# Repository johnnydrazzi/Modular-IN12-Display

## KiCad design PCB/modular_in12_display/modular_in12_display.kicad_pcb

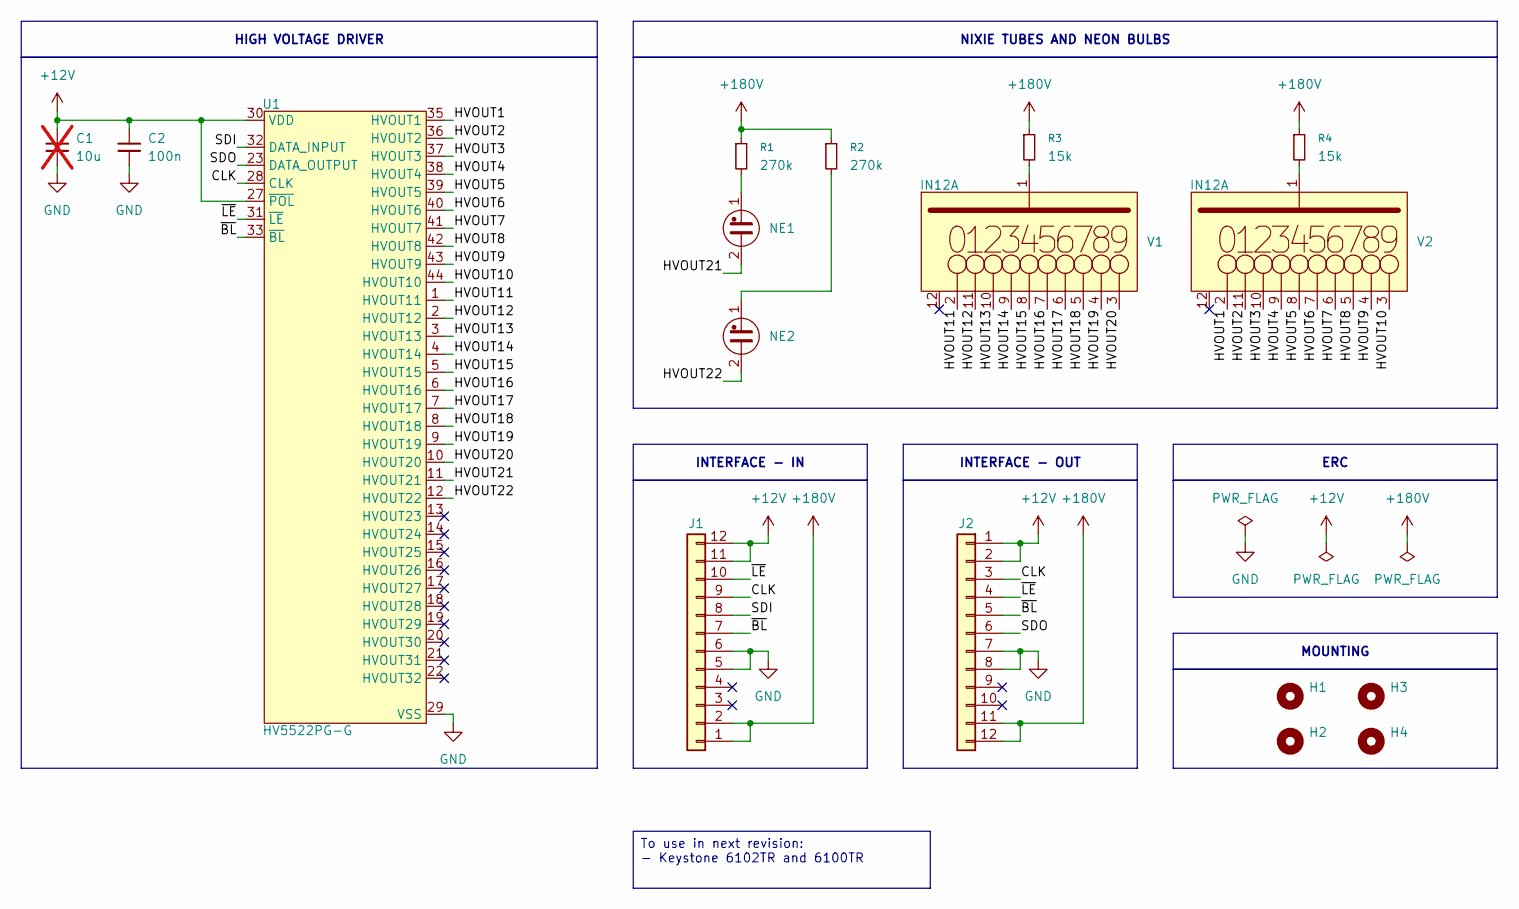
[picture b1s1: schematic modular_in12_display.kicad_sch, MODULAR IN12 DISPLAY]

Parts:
C1: 10u; C_1206_3216Metric; MPN CL31B106KBHNNNE; LCSC C89632; not fitted
C2: 100n; C_0805_2012Metric; MPN CL21B104KBCNNNC; LCSC C1711
H1, H2, H3, H4: MountingHole; MountingHole_3.2mm_M3_Pad
J1: IDC 10P Male Edge; MPN ZX-PZ2.54-2-6PZZ; LCSC C7501277
J2: IDC 10P Female Edge; MPN PM254-2-06-Z-8.5; LCSC C2897407
NE1, NE2: Lamp_Neon; Generic Neon Bulb; MPN INS-1
R1, R2: 270k; R_0805_2012Metric; MPN 0805W8F2703T5E; LCSC C17589
R3, R4: 15k; R_1206_3216Metric; MPN 1206W4F1502T5E; LCSC C25828
U1: HV5522PG-G; PQFP-44_10x10mm_P0.8mm; MPN HV5522PG-G
V1, V2: IN12A

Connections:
+12V: C1.1, C2.1, J1.11, J1.12, J2.1, J2.2, U1.27 (~POL), U1.30 (VDD)
+180V: J1.1, J1.2, J2.11, J2.12, R1.1, R2.1, R3.1, R4.1
/CLK: J1.9, J2.3, U1.28 (CLK)
/HVOUT1: U1.35 (HVOUT1), V2.2
/HVOUT2: U1.36 (HVOUT2), V2.11
/HVOUT3: U1.37 (HVOUT3), V2.10
/HVOUT4: U1.38 (HVOUT4), V2.9
/HVOUT5: U1.39 (HVOUT5), V2.8
/HVOUT6: U1.40 (HVOUT6), V2.7
/HVOUT7: U1.41 (HVOUT7), V2.6
/HVOUT8: U1.42 (HVOUT8), V2.5
/HVOUT9: U1.43 (HVOUT9), V2.4
/HVOUT10: U1.44 (HVOUT10), V2.3
/HVOUT11: U1.1 (HVOUT11), V1.2
/HVOUT12: U1.2 (HVOUT12), V1.11
/HVOUT13: U1.3 (HVOUT13), V1.10
/HVOUT14: U1.4 (HVOUT14), V1.9
/HVOUT15: U1.5 (HVOUT15), V1.8
/HVOUT16: U1.6 (HVOUT16), V1.7
/HVOUT17: U1.7 (HVOUT17), V1.6
/HVOUT18: U1.8 (HVOUT18), V1.5
/HVOUT19: U1.9 (HVOUT19), V1.4
/HVOUT20: U1.10 (HVOUT20), V1.3
/HVOUT21: NE1.2, U1.11 (HVOUT21)
/HVOUT22: NE2.2, U1.12 (HVOUT22)
/SDI: J1.8, U1.32 (DATA_INPUT)
/SDO: J2.6, U1.23 (DATA_OUTPUT)
/~BL: J1.7, J2.5, U1.33 (~BL)
/~LE: J1.10, J2.4, U1.31 (~LE)
GND: C1.2, C2.2, J1.5, J1.6, J2.7, J2.8, U1.29 (VSS)
unnamed: NE1.1, R1.2
unnamed: NE2.1, R2.2
unnamed: R3.2, V1.1
unnamed: R4.2, V2.1

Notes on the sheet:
HIGH VOLTAGE DRIVER
To use in next revision: - Keystone 6102TR and 6100TR
INTERFACE - IN
MOUNTING
INTERFACE - OUT
NIXIE TUBES AND NEON BULBS
ERC

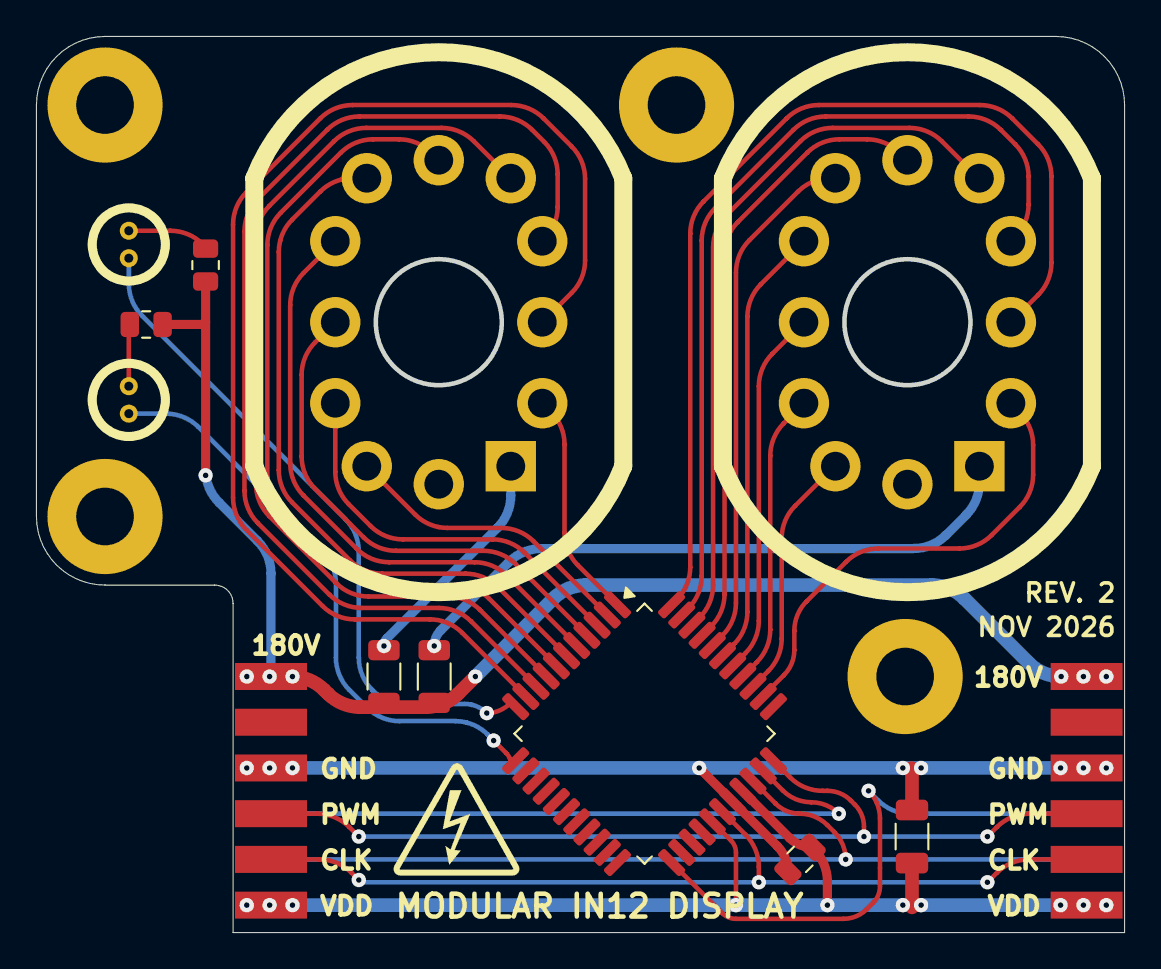
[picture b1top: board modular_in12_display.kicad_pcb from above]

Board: 2 copper layers, 60.5 x 49.8 mm, 17 parts (0 on the bottom side), 34 nets.
